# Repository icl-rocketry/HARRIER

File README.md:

# Project HARRIER

Solid-state particle detector for a rocket payload. Detects cosmic radiation
throughout flight and logs each hit with altitude, to build up counting
statistics post-flight.

Built in KiCad. Mixed-signal board: the detector board reads two independent
silicon-diode detector channels and logs events. 

## How it works 

A cosmic particle hits a reverse-biased photodiode and dumps a few femtocoulombs
of charge. A charge-sensitive amplifier turns that into a ~7 mV pulse, a
comparator checks it against a tunable threshold and the output signal is processed
by a seperate Pickle Rick board.

## Repository layout

The KiCad project has five schematic sheets:
Using the ICLR Board Template

| Sheet | Contents |
|-------|----------|
| Root | status LEDs, connectors, test points |
| Power Board | Three isolated rails off a ~7.4V battery: +25V bias, +5V analogue, +3.3V digital |
| Detector Board | The signal chain: diodes, charge amps, comparators (2 channels) |

## specs

- **Enclosure:** Circa 90 x 90 x 100 mm (TBD), light-tight detector housing
- **Power:** ~1.5 W from a ~7.4V battery (cell TBC)
- **Detector:** 2x BPW34 photodiodes, biased at +50V
- **Front-end:** ADA4817-1 charge amp, TLV3201 comparator, per channel
- **MCU:** ESP32-S3

## Status

Work in progress. Schematic of the detector front-end is nearly
complete; layout, bring-up, and firmware still to come.

**Outstanding before layout:**
- Confirm comparator edge polarity on the bench (rising vs falling) before
  writing interrupt firmware
- Clear all ERC

## Firmware

Firmware is set up for PlatformIO. Clone the repo and open in PlatformIO to
build and flash.

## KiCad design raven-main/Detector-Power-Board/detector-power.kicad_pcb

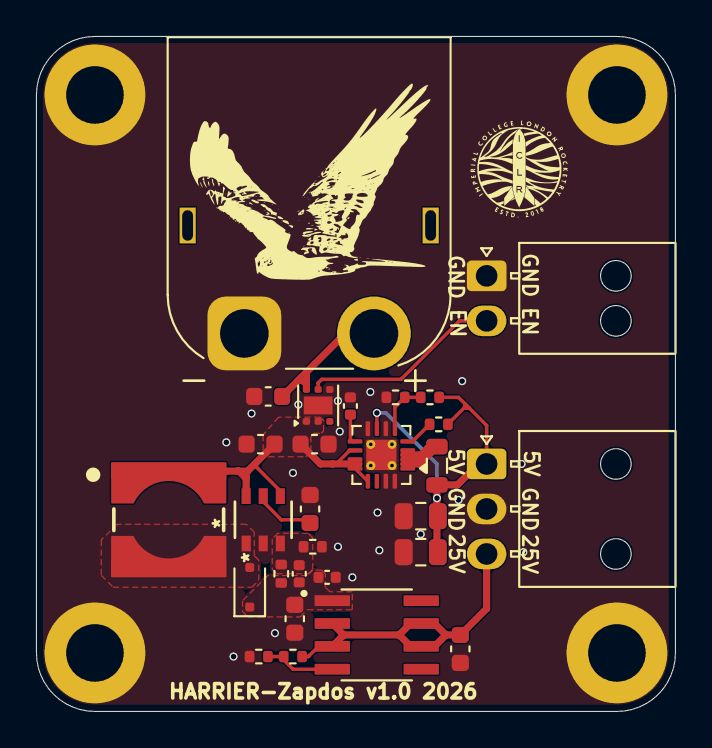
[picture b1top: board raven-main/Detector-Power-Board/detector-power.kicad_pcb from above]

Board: 2 copper layers, 35.5 x 37.5 mm, 32 parts (0 on the bottom side), 15 nets.

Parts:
C1, C3: 4.7uF 50V; C_0603_1608Metric
C2, C8: 4.7uF; C_0603_1608Metric
C4: 4.7pF 50V; C_0402_1005Metric
C5: 100nF 50V; C_0402_1005Metric
C6: 1uF 50V; C_0603_1608Metric
C7: 1uF; C_0603_1608Metric
C9, C10: 10uF; C_0805_2012Metric
C11: 620pF; C_0402_1005Metric
D1: PMEG6010CEJ; D_SOD-323F
H1, H2, H3, H4: MountingHole_Pad; MountingHole_3.2mm_M3_DIN965_Pad
J1: Conn_01x02_Pin; Molex_Nano-Fit_105313-xx02_1x02_P2.50mm_Horizontal
J2: DeployLipo; AMASS_XT60PW-M_1x02_P7.20mm_Horizontal
J3: Conn_01x03_Pin; Molex_Nano-Fit_105313-xx03_1x03_P2.50mm_Horizontal
L1: 6.8uH; WE-HEPC_6030
L2: 2.2uH; L_0805_2012Metric
R1: 162kΩ; R_0402_1005Metric
R2: 240Ω; R_0402_1005Metric
R3: 4.56kΩ; R_0402_1005Metric
R4: 10kΩ; R_0402_1005Metric
R5: 100kΩ; R_0402_1005Metric
R6: 953kΩ; R_0402_1005Metric
R7: 180kΩ; R_0402_1005Metric
U1: TPS22810DRV; WSON-6-1EP_2x2mm_P0.65mm_EP1x1.6mm
U2: LM317LIDR; SOIC127P599X175-8N
U3: LT8330IS6-TRMPBF; IC6_LT8330IS6-TRMPBF_ADI
U4: TPS62150; VQFN-16-1EP_3x3mm_P0.5mm_EP1.68x1.68mm_ThermalVias

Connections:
/BATT+: C1.1, J2.2, U1.6 (VIN)
/BBIN: C2.1, C8.1, L1.1, U1.1 (VOUT), U1.2 (QOD), U3.4 (EN/UVLO), U3.6 (VIN), U4.10 (VIN), U4.11 (VIN), U4.12 (VIN), U4.13 (EN)
/Filtered_Power_Out_25V: C6.1, J3.3, R2.1, U2.2 (VOUT), U2.3 (VOUT), U2.6 (VOUT), U2.7 (VOUT)
/ON-OFF: J1.2, U1.5 (EN/UVLO)
/Power_Out_5V: C9.1, C10.1, J3.1, L2.2, R5.1, R6.1, U4.7 (FSW), U4.14 (VOS)
/Power_Out_27.5V: C3.1, C4.1, C5.1, D1.1 (K), R1.1, U2.1 (VIN)
GND: C1.2, C2.2, C3.2, C5.2, C6.2, C7.2, C8.2, C9.2, C10.2, C11.2, H1.1 (1_1), H2.1 (1_1), H3.1 (1_1), H4.1 (1_1), J1.1, J2.1, J3.2, R3.2, R4.2, R7.2, U1.4 (GND), U1.7 (GND), U3.2 (GND), U4.6 (GND), U4.8 (DEF), U4.15 (GND), U4.16 (GND), U4.17 (GND)
unnamed: D1.2 (A), L1.2, U3.1 (SW)
unnamed: L2.1, U4.1 (SW), U4.2 (SW), U4.3 (SW)
unnamed: R2.2, R3.1, U2.4 (ADJUST)
unnamed: C4.2, R1.2, R4.1, U3.3 (FBX)
unnamed: C7.1, U3.5 (INTVCC)
unnamed: R6.2, R7.1, U4.5 (FB)
unnamed: R5.2, U4.4 (PG)
unnamed: C11.1, U4.9 (SS/TR)

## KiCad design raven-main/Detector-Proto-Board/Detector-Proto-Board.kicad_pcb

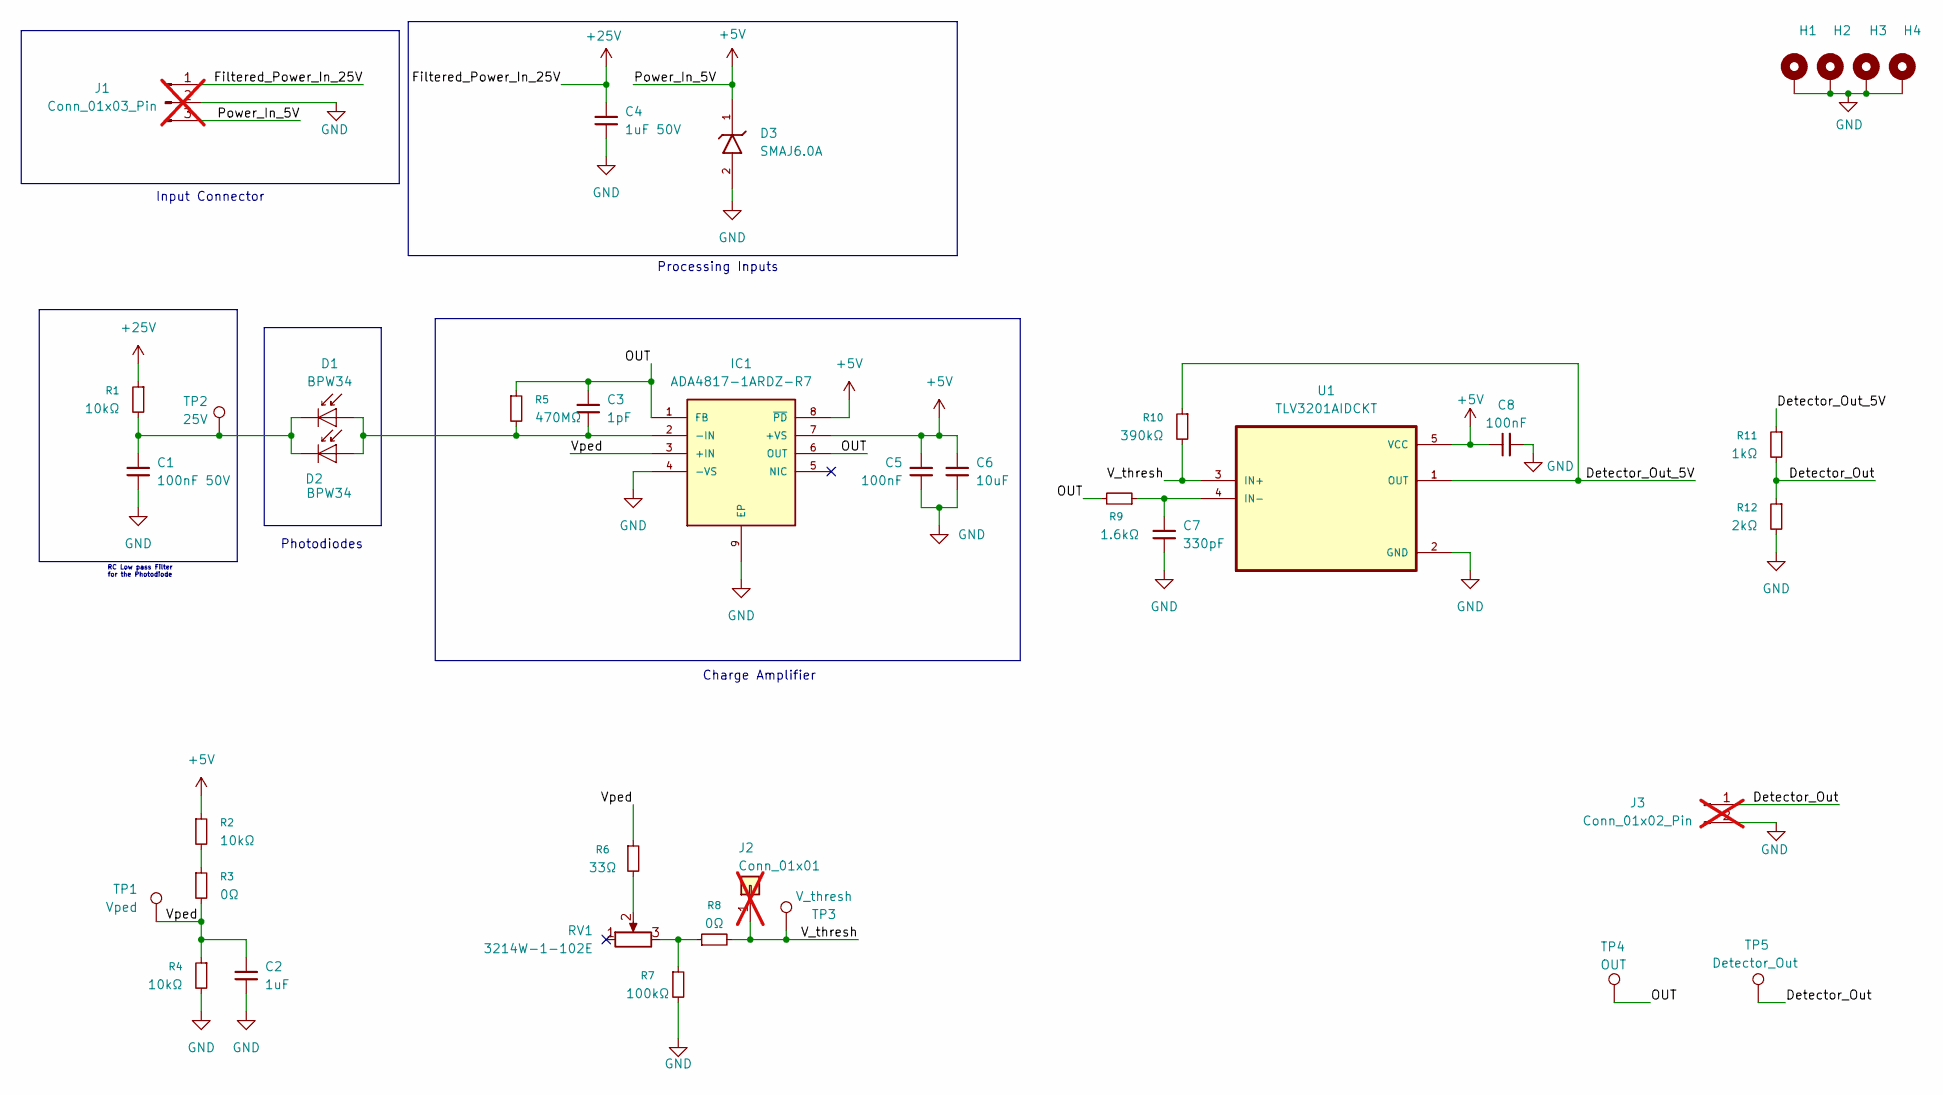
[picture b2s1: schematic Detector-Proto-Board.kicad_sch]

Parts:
C1: 100nF 50V; C_0402_1005Metric
C2: 1uF; C_0603_1608Metric
C3: 1pF; C_0402_1005Metric
C4: 1uF 50V; C_0603_1608Metric
C5, C8: 100nF; C_0402_1005Metric
C6: 10uF; C_0805_2012Metric
C7: 330pF; C_0402_1005Metric
D1, D2: BPW34; Osram_DIL2_4.3x4.65mm_P5.08mm
D3: SMAJ6.0A; D_SMA; MOUSER_PART_NUMBER 576-SMAJ5.0A
H1, H2, H3, H4: MountingHole_Pad; MountingHole_3.2mm_M3_DIN965_Pad
IC1: ADA4817-1ARDZ-R7; SOIC127P600X175-9N; Mouser_Part_Number 584-ADA4817-1ARDZ-R7
J1: Conn_01x03_Pin; Molex_Nano-Fit_105313-xx03_1x03_P2.50mm_Horizontal; not fitted
J2: Conn_01x01; PinHeader_1x01_P2.54mm_Vertical; not fitted
J3: Conn_01x02_Pin; Molex_Nano-Fit_105313-xx02_1x02_P2.50mm_Horizontal; not fitted
R1, R2, R4: 10kΩ; R_0402_1005Metric
R3, R8: 0Ω; R_0402_1005Metric
R5: 470MΩ; R_0603_1608Metric
R6: 33Ω; R_0402_1005Metric
R7: 100kΩ; R_0402_1005Metric
R9: 1.6kΩ; R_0402_1005Metric
R10: 390kΩ; R_0402_1005Metric
R11: 1kΩ; R_0402_1005Metric
R12: 2kΩ; R_0402_1005Metric
RV1: 3214W-1-102E; Potentiometer_Bourns_3214W_Vertical
TP1: Vped; TestPoint_Pad_D2.0mm
TP2: 25V; TestPoint_Pad_D2.0mm
TP3: V_thresh; TestPoint_Pad_D2.0mm
TP4: OUT; TestPoint_Pad_D2.0mm
TP5: Detector_Out; TestPoint_Pad_D2.0mm
U1: TLV3201AIDCKT; SOT65P210X110-5N

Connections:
+5V: C5.1, C6.1, C8.1, D3.1, IC1.7 (+VS), IC1.8 (~PD), J1.3, R2.1, U1.5 (VCC)
+25V: C4.1, J1.1, R1.1
/Detector_Out: J3.1, R11.2, R12.1, TP5.1 (1_1)
/Detector_Out_5V: R10.1, R11.1, U1.1 (OUT)
/OUT: C3.1, IC1.1 (FB), IC1.6 (OUT), R5.1, R9.2, TP4.1 (1_1)
/V_thresh: J2.1 (Pin_1_1), R8.2, R10.2, TP3.1 (1_1), U1.3 (IN+)
/Vped: C2.1, IC1.3 (+IN), R3.2, R4.1, R6.1, TP1.1 (1_1)
GND: C1.2, C2.2, C4.2, C5.2, C6.2, C7.2, C8.2, D3.2, H1.1 (1_1), H2.1 (1_1), H3.1 (1_1), H4.1 (1_1), IC1.4 (-VS), IC1.9 (EP), J1.2, J3.2, R4.2, R7.2, R12.2, U1.2 (GND)
unnamed: C3.2, D1.2 (A), D2.2 (A), IC1.2 (-IN), R5.2
unnamed: C1.1, D1.1 (K), D2.1 (K), R1.2, TP2.1 (1_1)
unnamed: R2.2, R3.1
unnamed: R6.2, RV1.2
unnamed: R7.1, R8.1, RV1.3
unnamed: C7.1, R9.1, U1.4 (IN-)

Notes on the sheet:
Photodiodes
Processing Inputs
RC Low pass Filter for the Photodiode
Charge Amplifier
Input Connector

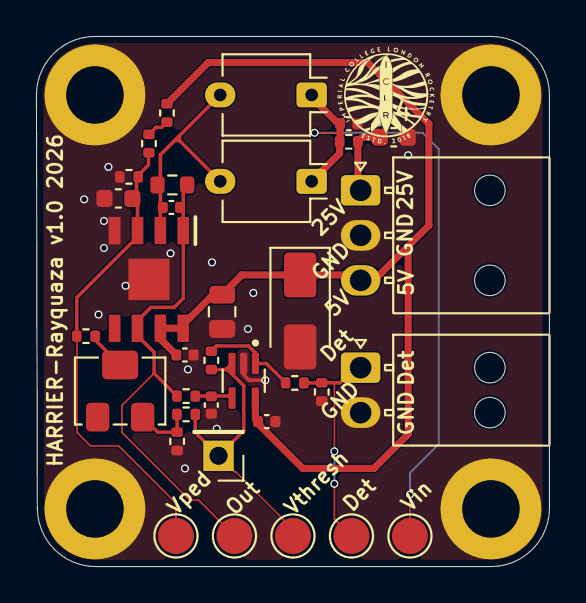
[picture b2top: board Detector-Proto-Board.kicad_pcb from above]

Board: 2 copper layers, 28.5 x 29.5 mm, 38 parts (0 on the bottom side), 14 nets.

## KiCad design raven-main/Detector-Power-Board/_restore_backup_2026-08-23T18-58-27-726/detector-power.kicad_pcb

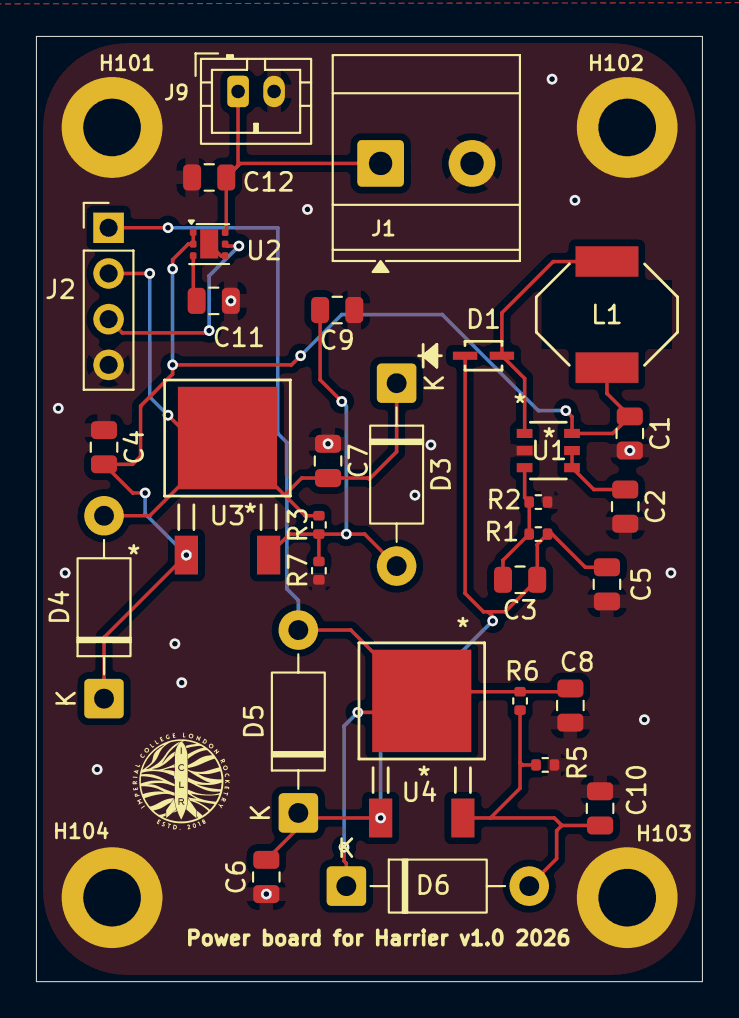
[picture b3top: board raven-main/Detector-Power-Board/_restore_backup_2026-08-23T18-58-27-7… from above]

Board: 2 copper layers, 37.0 x 52.5 mm, 35 parts (0 on the bottom side), 14 nets.

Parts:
C1, C5: 4.7u; C_0805_2012Metric
C2, C7, C8, C9, C10: 1u; C_0805_2012Metric
C3: 4.7p; C_0805_2012Metric
C4, C6: 0.1u; C_0805_2012Metric
C11: 1n; C_0805_2012Metric
C12: 5u; C_0805_2012Metric
D1: D_Schottky; SOD323F_NEX
D3, D4, D5, D6: 1N4002; D_DO-41_SOD81_P10.16mm_Horizontal
H101, H102, H103, H104: MountingHole_Pad; MountingHole_3.2mm_M3_DIN965_Pad
J1: DeployLipo; TerminalBlock_Phoenix_MKDS-3-2-5.08_1x02_P5.08mm_Horizontal
J2: Conn_01x04; PinHeader_1x04_P2.54mm_Vertical
J9: UCLipo; JST_PH_B2B-PH-K_1x02_P2.00mm_Vertical
L1: 8.2u; IND_8R0NC_SUM
R1: 162k; R_0402_1005Metric
R2: 10k; R_0402_1005Metric
R3, R6: 240; R_0402_1005Metric
R5: 4.56k; R_0402_1005Metric
R7: 720; R_0402_1005Metric
U1: LT8330IS6-TRMPBF; IC6_LT8330IS6-TRMPBF_ADI
U2: TPS22810DRV; WSON-6-1EP_2x2mm_P0.65mm_EP1x1.6mm
U3, U4: LM317LCLPRE3; TD03B_TEX

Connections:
/BBIN: C1.1, C4.2, D4.1 (K), L1.1, U1.6 (VIN), U2.1 (VOUT), U2.2 (QOD), U3.1 (INPUT)
/Filtered_Power_Out_25V: C8.2, D5.2 (A), D6.1 (K), J2.1, R6.2, U4.2 (OUTPUT)
/ON-OFF: J2.3, U2.5 (EN/UVLO)
/Power_Out_5V: C7.2, D3.1 (K), D4.2 (A), J2.2, R3.2, U3.2 (OUTPUT)
/Power_Out_27.5V: C3.1, C5.1, C6.2, D1.1 (K), D5.1 (K), R1.1, U4.1 (INPUT)
GND: C1.2, C2.2, C4.1, C5.2, C6.1, C7.1, C8.1, C9.1, C10.1, C11.2, C12.2, H101.1 (1_1), H102.1 (1_1), H103.1 (1_1), H104.1 (1_1), J1.2, J2.4, J9.2, R2.2, R5.1, R7.1, U1.2 (GND)
unnamed: D1.2 (A), L1.2, U1.1 (SW)
unnamed: C9.2, D3.2 (A), R3.1, R7.2, U3.3 (ADJUSTMENT)
unnamed: C10.2, D6.2 (A), R5.2, R6.1, U4.3 (ADJUSTMENT)
unnamed: C12.1, J1.1, J9.1, U2.6 (VIN)
unnamed: C2.1, U1.4 (EN/UVLO), U1.5 (INTVCC)
unnamed: C3.2, R1.2, R2.1, U1.3 (FBX)
unnamed: C11.1, U2.3 (CT)
unnamed: U2.4 (GND), U2.7 (GND)
